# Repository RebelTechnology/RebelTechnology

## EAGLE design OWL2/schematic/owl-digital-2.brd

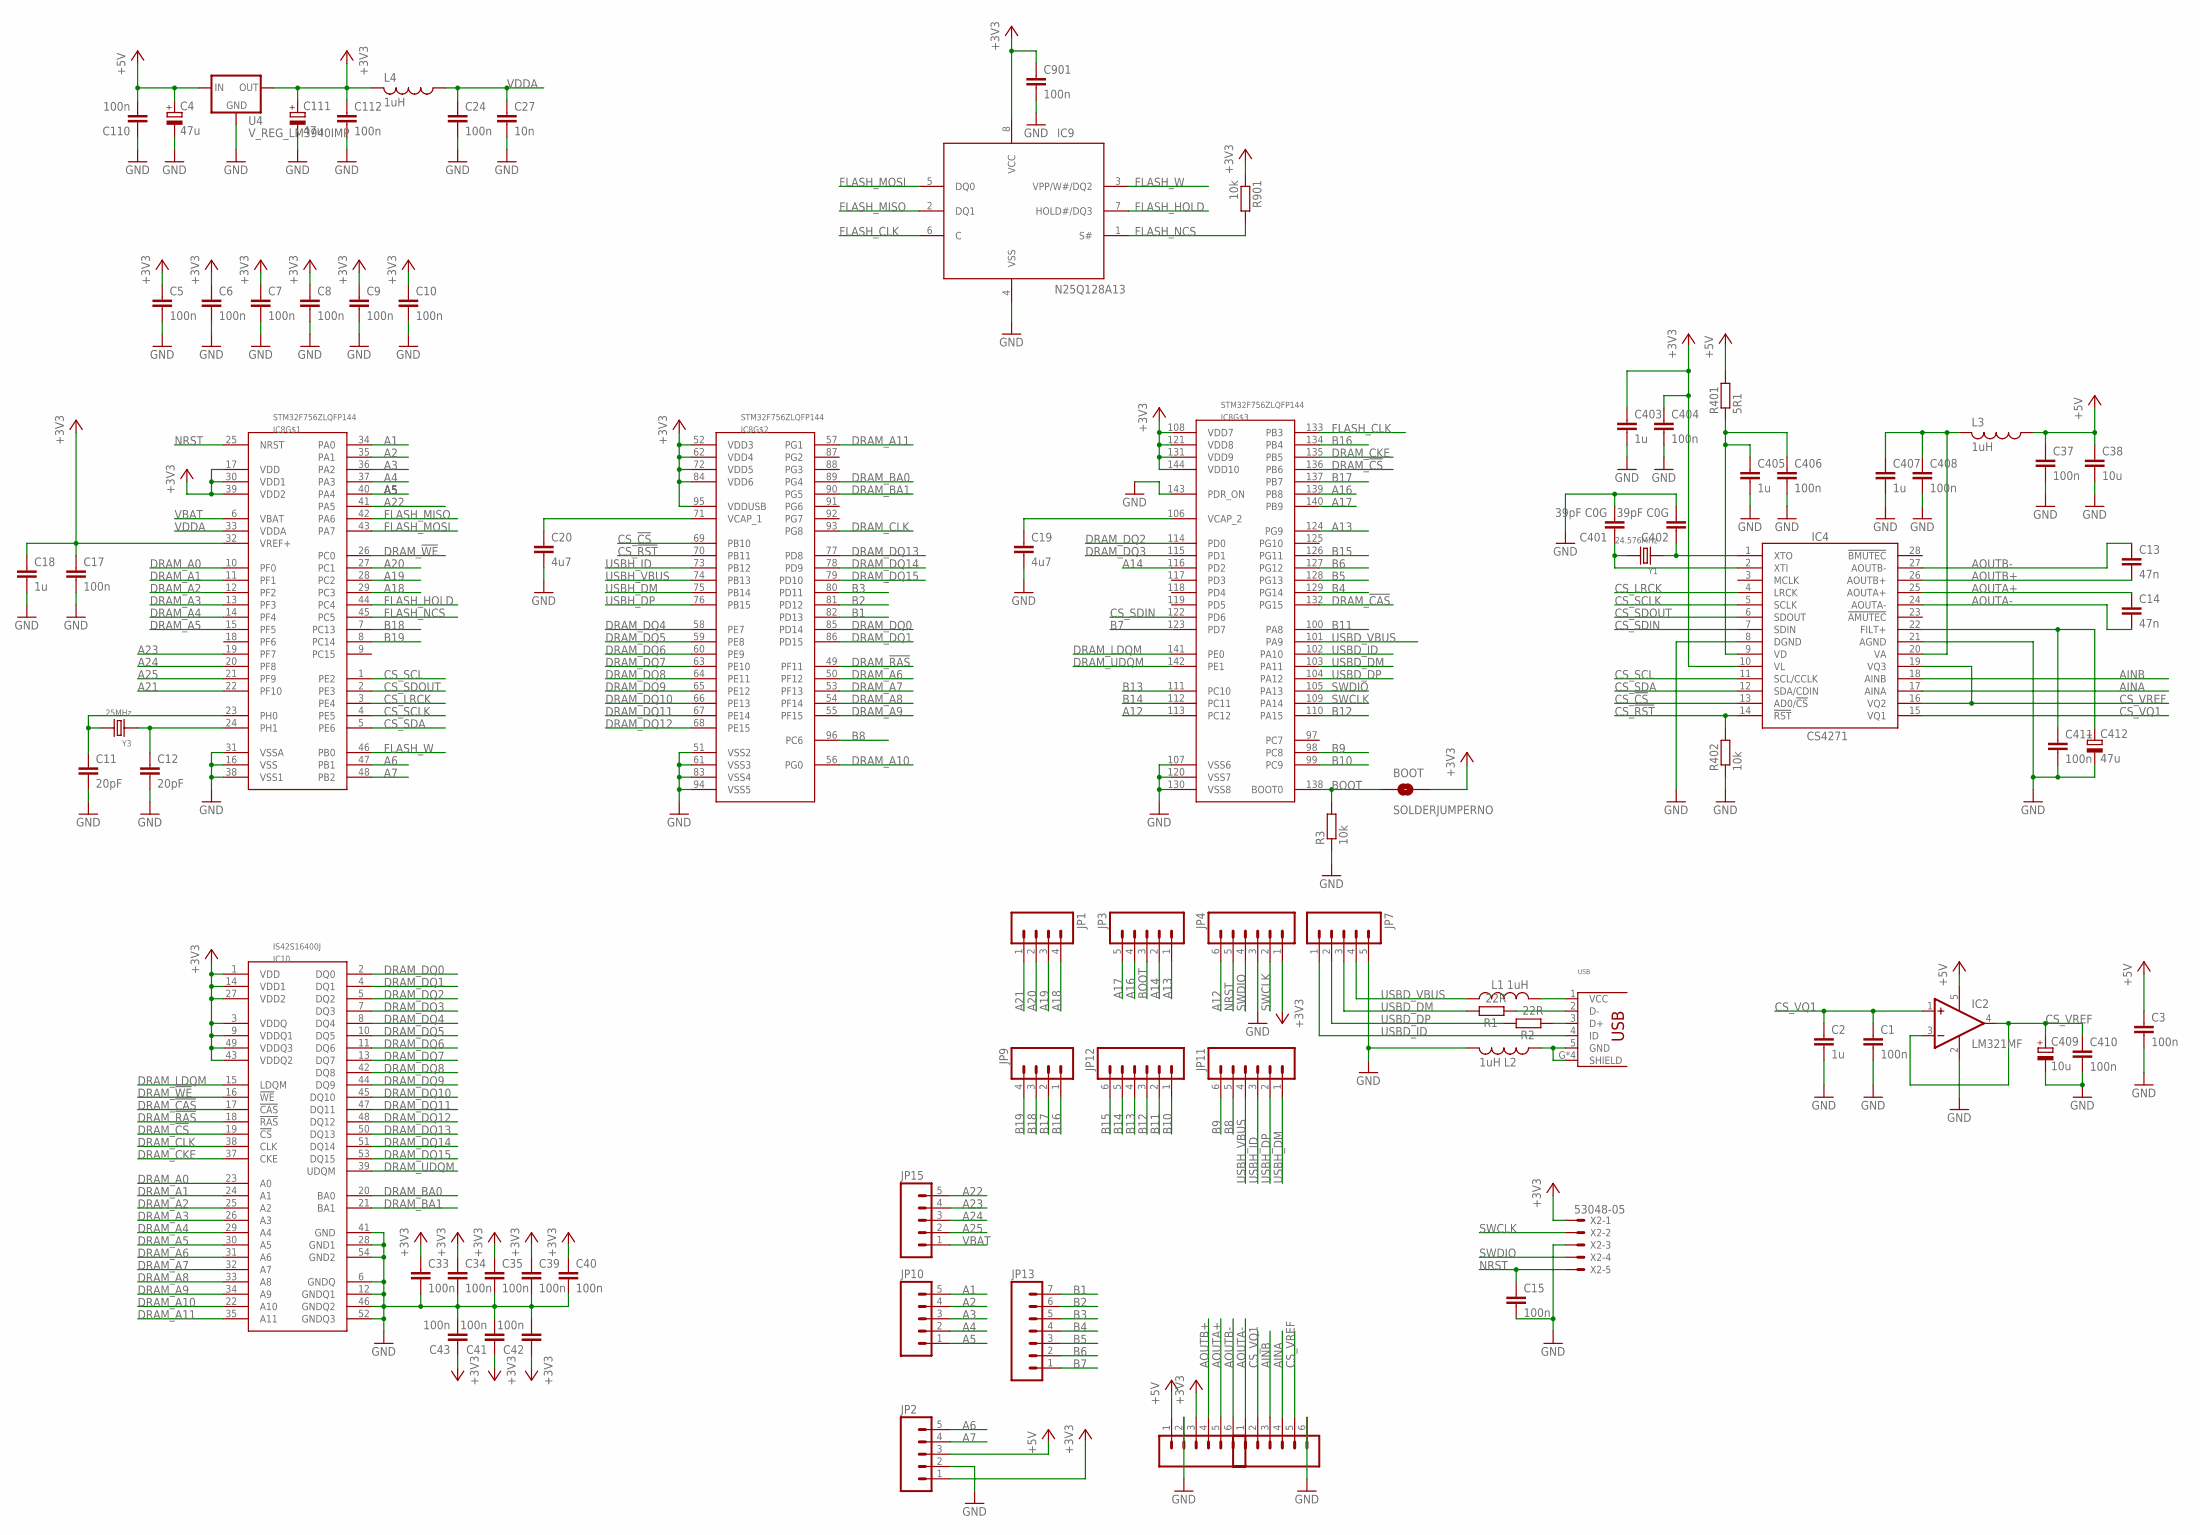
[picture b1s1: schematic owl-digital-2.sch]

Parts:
BOOT: SOLDERJUMPERNO; SJ_2S-NO
C1, C3, C5, C6, C7, C8, C9, C10, C15, C17, C24, C33, C34, C35, C37, C39, C40, C41, C42, C43, C110, C112, C404, C406, C408, C410, C411, C901: 100n; C0603
C2, C18, C403, C405, C407: 1u; C0603
C4, C111, C412: 47u; CPOL-5
C11, C12: 20pF; C0603
C13, C14: 47n; C0603
C19, C20: 4u7; C0603
C27: 10n; C0603
C38: 10u; C1206
C401, C402: 39pF C0G; C0603
C409: 10u; CPOL-5
IC2: LM321MF; SOT23-5
IC4: CS4271; TSSOP28-0.65-9.7X4.4MM
IC8: STM32F756ZLQFP144; QFP50P2200X2200X160-144N
IC9: N25Q128A13; SO8W
IC10: IS42S16400J; TSOP54-400
JP1, JP9: M04PTH; 1X04
JP2, JP3, JP7, JP10, JP15: M05PTH; 1X05
JP4, JP5, JP6, JP11, JP12: M06SIP; 1X06
JP13: M07; 1X07
L1, L2, L3, L4: 1uH; 0603
R1, R2: 22R; 0603
R3, R402, R901: 10k; 0603
R401: 5R1; 0603
U4: V_REG_LM3940IMP; SOT223
USB: USB_HRS_ZX62-B-5PA(11)MICRO.B; HRS_ZX62RD-AB-5P8
X2: 53048-05
Y1: 24.576MHz; X2-SMD-5.0X3.2X1.3MM
Y3: 25MHz; X2-SMD-5.0X3.2X1.3MM

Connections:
+3V3: BOOT.2, C5.1, C6.1, C7.1, C8.1, C9.1, C10.1, C17.1, C18.1, C33.1, C34.1, C35.1, C39.1, C40.1, C41.1, C42.1, C43.1, C111.+, C112.1, C403.1, C404.1, C901.1, IC4.10 (VL), IC8.17 (VDD), IC8.30 (VDD1), IC8.32 (VREF+), IC8.39 (VDD2), IC8.52 (VDD3), IC8.62 (VDD4), IC8.72 (VDD5), IC8.84 (VDD6), IC8.95 (VDDUSB), IC8.108 (VDD7), IC8.121 (VDD8), IC8.131 (VDD9), IC8.144 (VDD10), IC9.8 (VCC), IC10.1 (VDD), IC10.3 (VDDQ), IC10.9 (VDDQ1), IC10.14 (VDD1), IC10.27 (VDD2), IC10.43 (VDDQ2), IC10.49 (VDDQ3), JP2.1, JP4.1, JP5.3, L4.2, R901.1, U4.3 (OUT), X2.1
+5V: C3.1, C4.+, C37.1, C38.1, C110.2, IC2.5 (V+), JP2.3, JP5.1, L3.1, R401.2, U4.1 (IN)
A1: IC8.34 (PA0), JP10.5
A2: IC8.35 (PA1), JP10.4
A3: IC8.36 (PA2), JP10.3
A4: IC8.37 (PA3), JP10.2
A5: IC8.40 (PA4), JP10.1
A6: IC8.47 (PB1), JP2.5
A7: IC8.48 (PB2), JP2.4
A12: IC8.113 (PC12), JP4.6
A13: IC8.124 (PG9), JP3.1
A14: IC8.116 (PD2), JP3.2
A16: IC8.139 (PB8), JP3.4
A17: IC8.140 (PB9), JP3.5
A18: IC8.29 (PC3), JP1.4
A19: IC8.28 (PC2), JP1.3
A20: IC8.27 (PC1), JP1.2
A21: IC8.22 (PF10), JP1.1
A22: IC8.41 (PA5), JP15.5
A23: IC8.19 (PF7), JP15.4
A24: IC8.20 (PF8), JP15.3
A25: IC8.21 (PF9), JP15.2
AINA: IC4.17 (AINA), JP6.4
AINB: IC4.18 (AINB), JP6.3
AOUTA+: C14.1, IC4.25 (AOUTA+), JP5.5
AOUTA-: C14.2, IC4.24 (AOUTA-), JP6.1
AOUTB+: C13.2, IC4.26 (AOUTB+), JP5.4
AOUTB-: C13.1, IC4.27 (AOUTB-), JP5.6
B1: IC8.82 (PD13), JP13.7
B2: IC8.81 (PD12), JP13.6
B3: IC8.80 (PD11), JP13.5
B4: IC8.129 (PG14), JP13.4
B5: IC8.128 (PG13), JP13.3
B6: IC8.127 (PG12), JP13.2
B7: IC8.123 (PD7), JP13.1
B8: IC8.96 (PC6), JP11.5
B9: IC8.98 (PC8), JP11.6
B10: IC8.99 (PC9), JP12.1
B11: IC8.100 (PA8), JP12.2
B12: IC8.110 (PA15), JP12.3
B13: IC8.111 (PC10), JP12.4
B14: IC8.112 (PC11), JP12.5
B15: IC8.126 (PG11), JP12.6
B16: IC8.134 (PB4), JP9.1
B17: IC8.137 (PB7), JP9.2
B18: IC8.7 (PC13), JP9.3
B19: IC8.8 (PC14), JP9.4
BOOT: BOOT.1, IC8.138 (BOOT0), JP3.3, R3.2
CS_!CS: IC4.13 (AD0/!CS), IC8.69 (PB10)
CS_!RST: IC4.14 (!RST), IC8.70 (PB11), R402.2
CS_LRCK: IC4.4 (LRCK), IC8.3 (PE4)
CS_SCL: IC4.11 (SCL/CCLK), IC8.1 (PE2)
CS_SCLK: IC4.5 (SCLK), IC8.4 (PE5)
CS_SDA: IC4.12 (SDA/CDIN), IC8.5 (PE6)
CS_SDIN: IC4.7 (SDIN), IC8.122 (PD6)
CS_SDOUT: IC4.6 (SDOUT), IC8.2 (PE3)
CS_VQ1: C1.1, C2.1, IC2.1 (+IN), IC4.15 (VQ1), JP6.2
CS_VREF: C409.+, C410.1, IC2.3 (-IN), IC2.4 (OUT), IC4.16 (VQ2), IC4.19 (VQ3), JP6.5
DRAM_!CAS: IC8.132 (PG15), IC10.17 (!CAS)
DRAM_!CS: IC8.136 (PB6), IC10.19 (!CS)
DRAM_!RAS: IC8.49 (PF11), IC10.18 (!RAS)
DRAM_!WE: IC8.26 (PC0), IC10.16 (!WE)
DRAM_A0: IC8.10 (PF0), IC10.23 (A0)
DRAM_A1: IC8.11 (PF1), IC10.24 (A1)
DRAM_A2: IC8.12 (PF2), IC10.25 (A2)
DRAM_A3: IC8.13 (PF3), IC10.26 (A3)
DRAM_A4: IC8.14 (PF4), IC10.29 (A4)
DRAM_A5: IC8.15 (PF5), IC10.30 (A5)
DRAM_A6: IC8.50 (PF12), IC10.31 (A6)
DRAM_A7: IC8.53 (PF13), IC10.32 (A7)
DRAM_A8: IC8.54 (PF14), IC10.33 (A8)
DRAM_A9: IC8.55 (PF15), IC10.34 (A9)
DRAM_A10: IC8.56 (PG0), IC10.22 (A10)
DRAM_A11: IC8.57 (PG1), IC10.35 (A11)
DRAM_BA0: IC8.89 (PG4), IC10.20 (BA0)
DRAM_BA1: IC8.90 (PG5), IC10.21 (BA1)
DRAM_CKE: IC8.135 (PB5), IC10.37 (CKE)
DRAM_CLK: IC8.93 (PG8), IC10.38 (CLK)
DRAM_DQ0: IC8.85 (PD14), IC10.2 (DQ0)
DRAM_DQ1: IC8.86 (PD15), IC10.4 (DQ1)
DRAM_DQ2: IC8.114 (PD0), IC10.5 (DQ2)
DRAM_DQ3: IC8.115 (PD1), IC10.7 (DQ3)
DRAM_DQ4: IC8.58 (PE7), IC10.8 (DQ4)
DRAM_DQ5: IC8.59 (PE8), IC10.10 (DQ5)
DRAM_DQ6: IC8.60 (PE9), IC10.11 (DQ6)
DRAM_DQ7: IC8.63 (PE10), IC10.13 (DQ7)
DRAM_DQ8: IC8.64 (PE11), IC10.42 (DQ8)
DRAM_DQ9: IC8.65 (PE12), IC10.44 (DQ9)
DRAM_DQ10: IC8.66 (PE13), IC10.45 (DQ10)
DRAM_DQ11: IC8.67 (PE14), IC10.47 (DQ11)
DRAM_DQ12: IC8.68 (PE15), IC10.48 (DQ12)
DRAM_DQ13: IC8.77 (PD8), IC10.50 (DQ13)
DRAM_DQ14: IC8.78 (PD9), IC10.51 (DQ14)
DRAM_DQ15: IC8.79 (PD10), IC10.53 (DQ15)
DRAM_LDQM: IC8.141 (PE0), IC10.15 (LDQM)
DRAM_UDQM: IC8.142 (PE1), IC10.39 (UDQM)
FLASH_CLK: IC8.133 (PB3), IC9.6 (C)
FLASH_HOLD: IC8.44 (PC4), IC9.7 (HOLD#/DQ3)
FLASH_MISO: IC8.42 (PA6), IC9.2 (DQ1)
FLASH_MOSI: IC8.43 (PA7), IC9.5 (DQ0)
FLASH_NCS: IC8.45 (PC5), IC9.1 (S#), R901.2
FLASH_W: IC8.46 (PB0), IC9.3 (VPP/W#/DQ2)
GND: C1.2, C2.2, C3.2, C4.-, C5.2, C6.2, C7.2, C8.2, C9.2, C10.2, C11.2, C12.2, C15.2, C17.2, C18.2, C19.2, C20.2, C24.2, C27.2, C33.2, C34.2, C35.2, C37.2, C38.2, C39.2, C40.2, C41.2, C42.2, C43.2, C110.1, C111.-, C112.2, C401.2, C402.2, C403.2, C404.2, C405.2, C406.2, C407.2, C408.2, C409.-, C410.2, C411.2, C412.-, C901.2, IC2.2 (V-), IC4.8 (DGND), IC4.21 (AGND), IC8.16 (VSS), IC8.31 (VSSA), IC8.38 (VSS1), IC8.51 (VSS2), IC8.61 (VSS3), IC8.83 (VSS4), IC8.94 (VSS5), IC8.107 (VSS6), IC8.120 (VSS7), IC8.130 (VSS8), IC8.143 (PDR_ON), IC9.4 (VSS), IC10.6 (GNDQ), IC10.12 (GNDQ1), IC10.28 (GND1), IC10.41 (GND), IC10.46 (GNDQ2), IC10.52 (GNDQ3), IC10.54 (GND2), JP2.2, JP4.3, JP5.2, JP6.6, JP7.5, L2.2, R3.1, R402.1, U4.2 (GND), X2.3
unnamed: L2.1, USB.5 (GND), USB.G (SHIELD), USB.G2 (SHIELD), USB.G3 (SHIELD), USB.G4 (SHIELD)
unnamed: L1.2, USB.1 (VCC)
unnamed: R2.1, USB.3 (D+)
unnamed: R1.1, USB.2 (D-)
unnamed: C12.1, IC8.24 (PH1), Y3.1
unnamed: C11.1, IC8.23 (PH0), Y3.2
unnamed: C402.1, IC4.1 (XTO), Y1.1
unnamed: C411.1, C412.+, IC4.22 (FILT+)
unnamed: C401.1, IC4.2 (XTI), Y1.2
unnamed: C19.1, IC8.106 (VCAP_2)
unnamed: C20.1, IC8.71 (VCAP_1)
NRST: C15.1, IC8.25 (NRST), JP4.5, X2.5
SWCLK: IC8.109 (PA14), JP4.2, X2.2
SWDIO: IC8.105 (PA13), JP4.4, X2.4
USBD_DM: IC8.103 (PA11), JP7.3, R1.2
USBD_DP: IC8.104 (PA12), JP7.2, R2.2
USBD_ID: IC8.102 (PA10), JP7.1, USB.4 (ID)
USBD_VBUS: IC8.101 (PA9), JP7.4, L1.1
USBH_DM: IC8.75 (PB14), JP11.1
USBH_DP: IC8.76 (PB15), JP11.2
USBH_ID: IC8.73 (PB12), JP11.3
USBH_VBUS: IC8.74 (PB13), JP11.4
VA: C407.1, C408.1, IC4.20 (VA), L3.2
VBAT: IC8.6 (VBAT), JP15.1
VD: C405.1, C406.1, IC4.9 (VD), R401.1
VDDA: C24.1, C27.1, IC8.33 (VDDA), L4.1

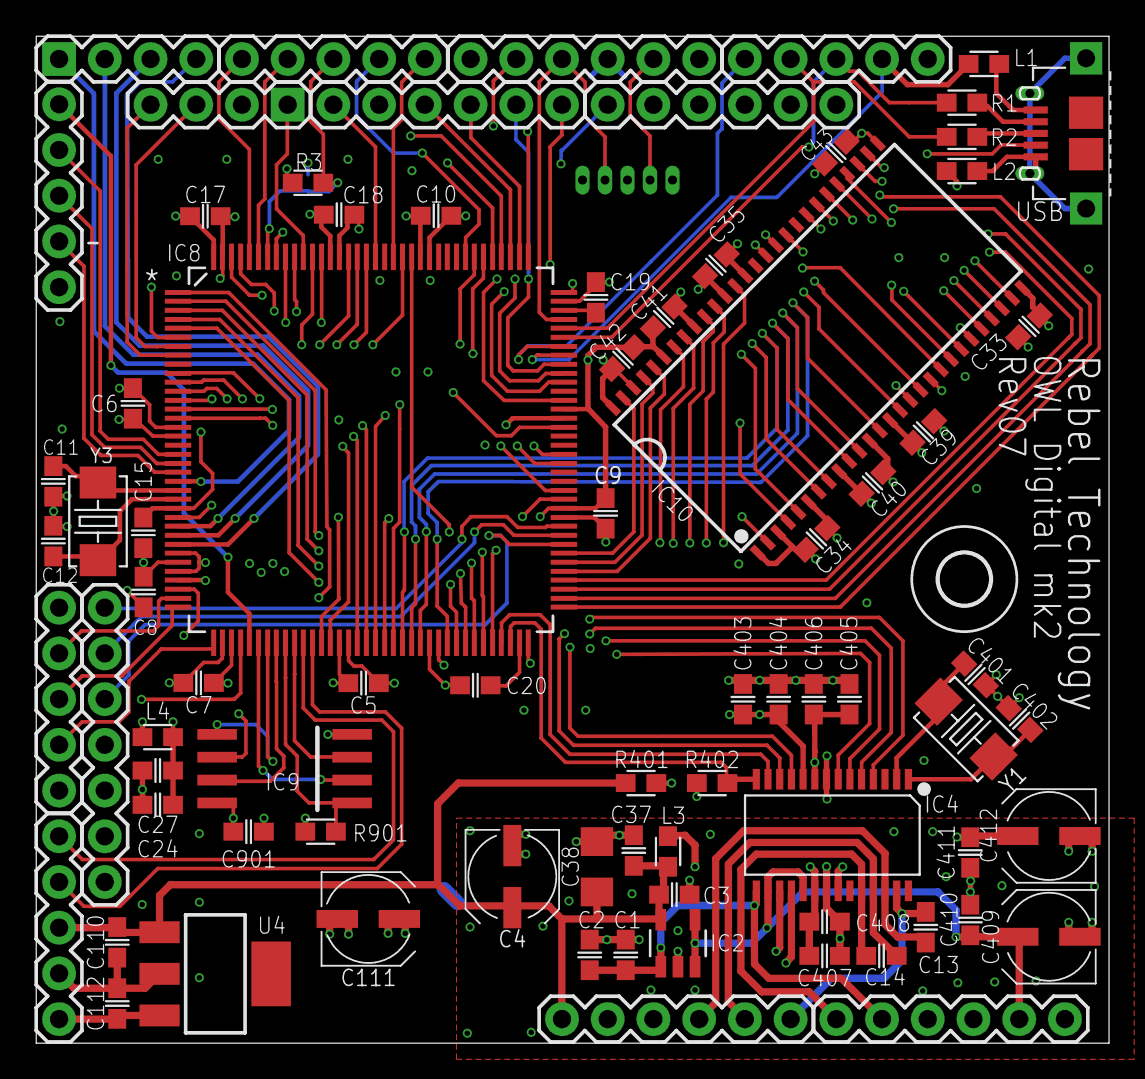
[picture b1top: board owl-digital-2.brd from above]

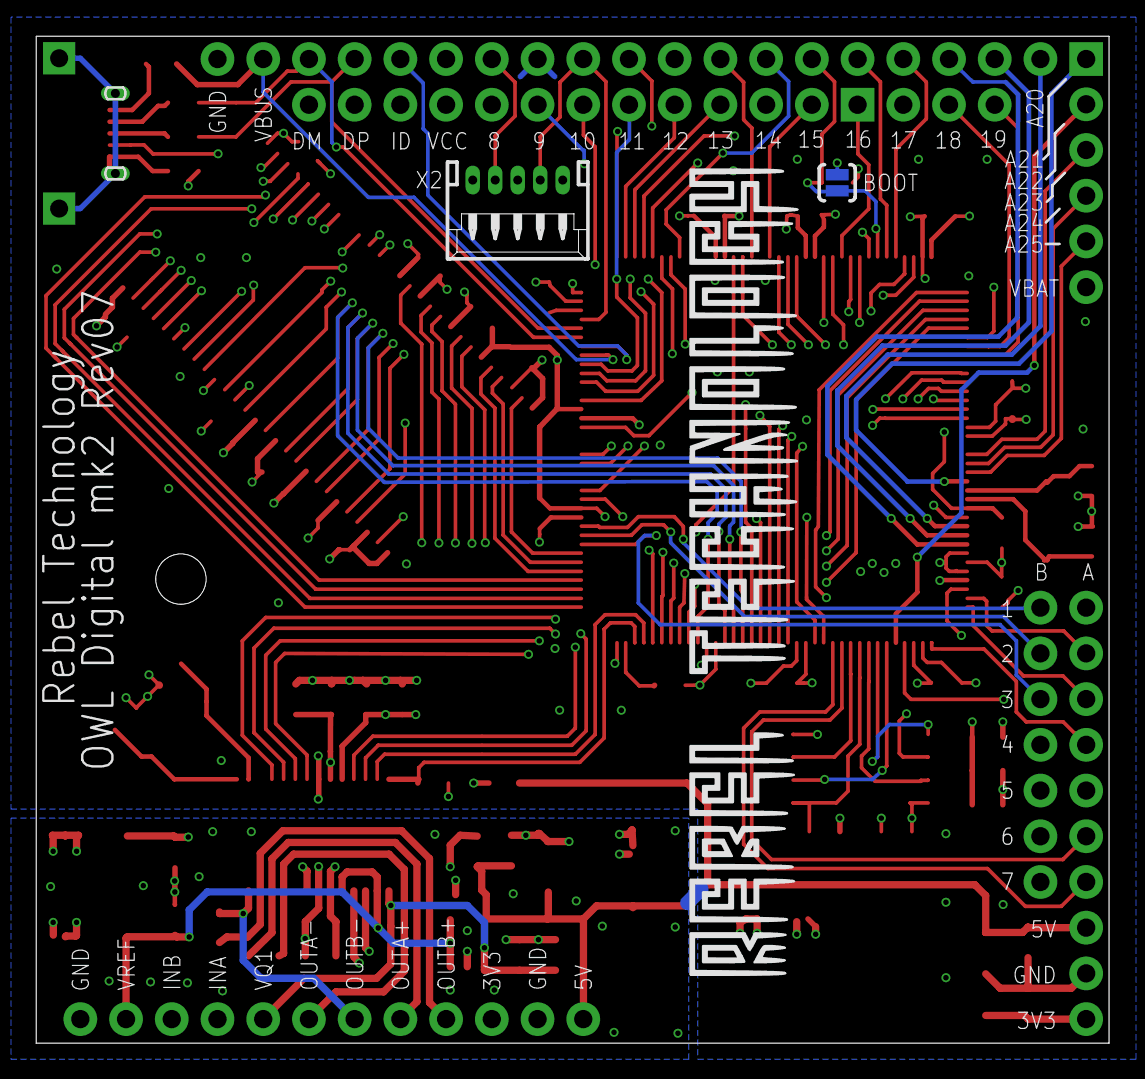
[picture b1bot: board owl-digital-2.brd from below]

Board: 4 copper layers, 59.6 x 55.9 mm, 82 parts (2 on the bottom side), 129 nets.

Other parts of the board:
U$1: 2,8

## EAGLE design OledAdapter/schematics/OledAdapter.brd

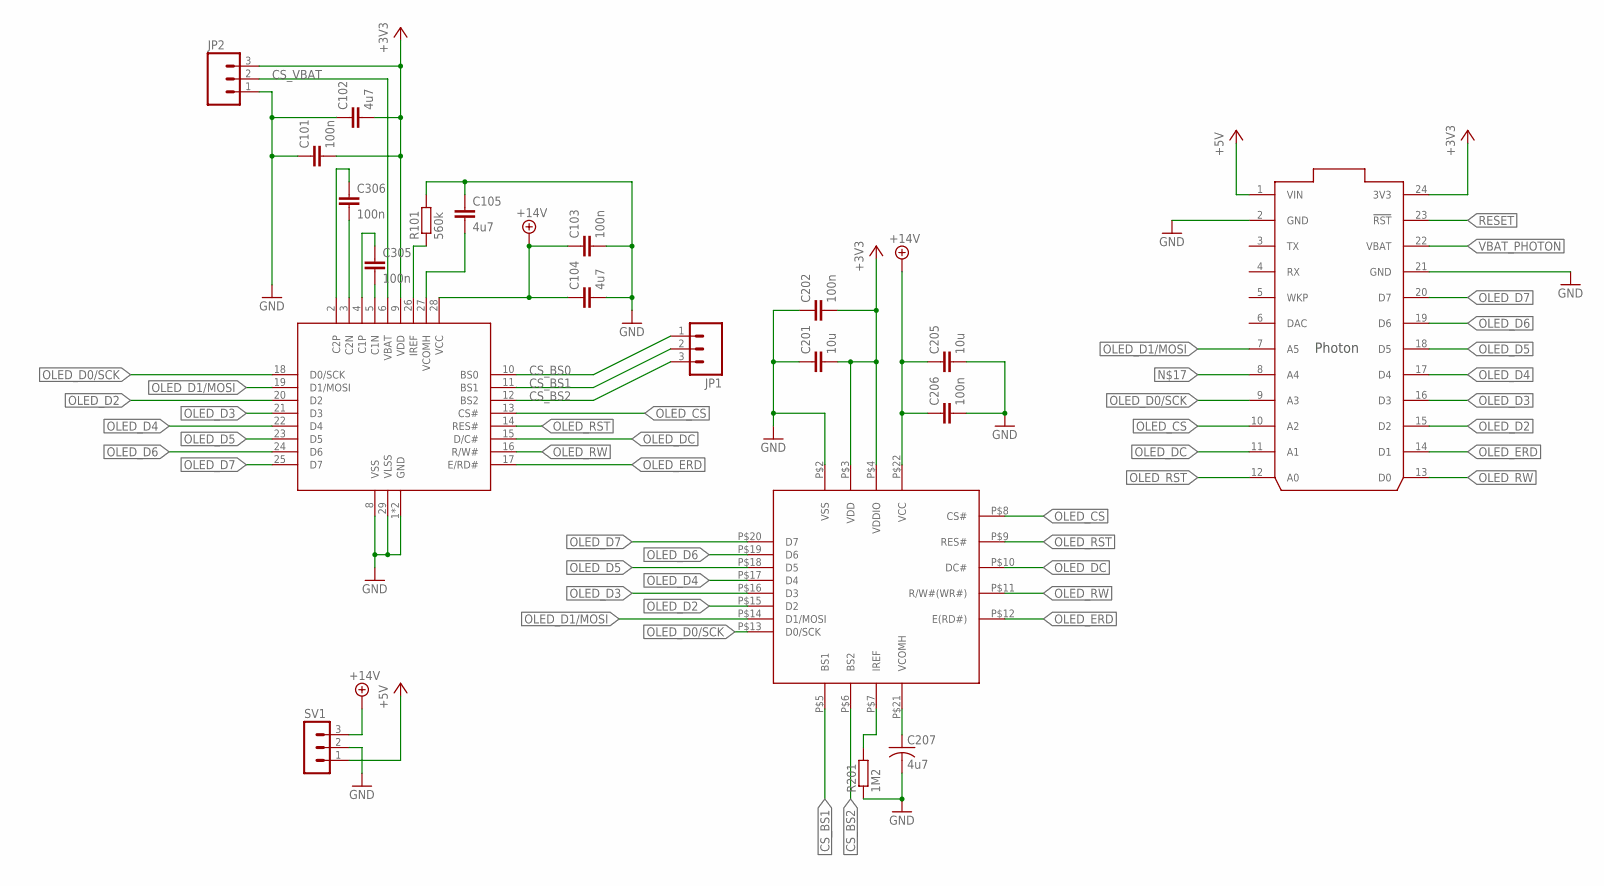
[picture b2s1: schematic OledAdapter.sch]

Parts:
C101, C103, C202, C206, C305, C306: 100n; C0603
C102, C104, C105, C207: 4u7; C0603
C201, C205: 10u; C0603
JP1, JP2: M03PTH; 1X03
R101: 560k; R0603
R201: 1M2; R0603
SV1: MA03-1
U$1: MCOT128064NZ-YM
U$2: PHOTON_WITH_HEADERS; PHOTON
U$3: MCOT096064AZ-RGBM

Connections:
+3V3: C101.2, C102.2, C201.2, C202.2, JP2.3, U$1.9 (VDD), U$2.24 (3V3), U$3.P$3 (VDD), U$3.P$4 (VDDIO)
+5V: SV1.1, U$2.1 (VIN)
+14V: C103.1, C104.1, C205.1, C206.1, SV1.3, U$1.28 (VCC), U$3.P$22 (VCC)
CS_BS0: JP1.1, U$1.10 (BS0)
CS_BS1: JP1.2, U$1.11 (BS1), U$3.P$5 (BS1)
CS_BS2: JP1.3, U$1.12 (BS2), U$3.P$6 (BS2)
CS_VBAT: JP2.2, U$1.6 (VBAT)
GND: C101.1, C102.1, C103.2, C104.2, C105.1, C201.1, C202.1, C205.2, C206.2, C207.2, JP2.1, R101.2, R201.1, SV1.2, U$1.1 (GND), U$1.8 (VSS), U$1.29 (VLSS), U$1.30 (GND), U$2.2 (GND), U$2.21 (GND), U$3.P$2 (VSS)
unnamed: C305.2, U$1.5 (C1N)
unnamed: C305.1, U$1.4 (C1P)
unnamed: C306.2, U$1.3 (C2N)
unnamed: R101.1, U$1.26 (IREF)
unnamed: C207.1, U$3.P$21 (VCOMH)
unnamed: C105.2, U$1.27 (VCOMH)
unnamed: R201.2, U$3.P$7 (IREF)
unnamed: C306.1, U$1.2 (C2P)
OLED_CS: U$1.13 (CS#), U$2.10 (A2), U$3.P$8 (CS#)
OLED_D0/SCK: U$1.18 (D0/SCK), U$2.9 (A3), U$3.P$13 (D0/SCK)
OLED_D1/MOSI: U$1.19 (D1/MOSI), U$2.7 (A5), U$3.P$14 (D1/MOSI)
OLED_D2: U$1.20 (D2), U$2.15 (D2), U$3.P$15 (D2)
OLED_D3: U$1.21 (D3), U$2.16 (D3), U$3.P$16 (D3)
OLED_D4: U$1.22 (D4), U$2.17 (D4), U$3.P$17 (D4)
OLED_D5: U$1.23 (D5), U$2.18 (D5), U$3.P$18 (D5)
OLED_D6: U$1.24 (D6), U$2.19 (D6), U$3.P$19 (D6)
OLED_D7: U$1.25 (D7), U$2.20 (D7), U$3.P$20 (D7)
OLED_DC: U$1.15 (D/C#), U$2.11 (A1), U$3.P$10 (DC#)
OLED_ERD: U$1.17 (E/RD#), U$2.14 (D1), U$3.P$12 (E(RD#))
OLED_RST: U$1.14 (RES#), U$2.12 (A0), U$3.P$9 (RES#)
OLED_RW: U$1.16 (R/W#), U$2.13 (D0), U$3.P$11 (R/W#(WR#))
RESET: U$2.23 (!RST)
VBAT_PHOTON: U$2.22 (VBAT)

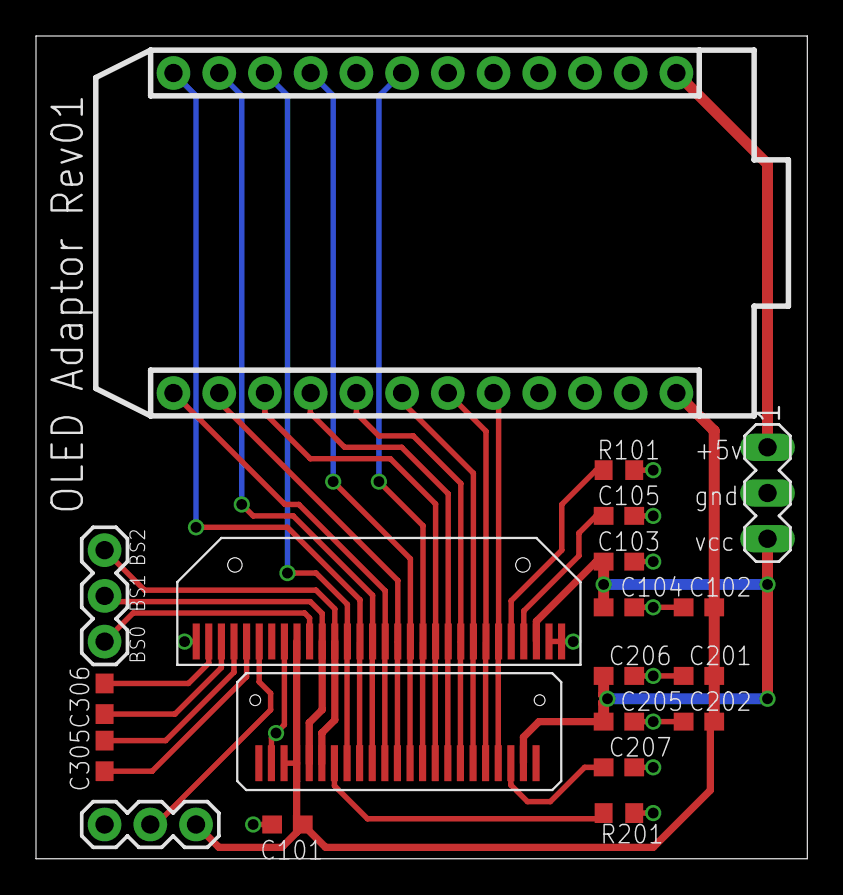
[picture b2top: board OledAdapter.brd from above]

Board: 2 copper layers, 42.9 x 45.7 mm, 20 parts (0 on the bottom side), 29 nets.

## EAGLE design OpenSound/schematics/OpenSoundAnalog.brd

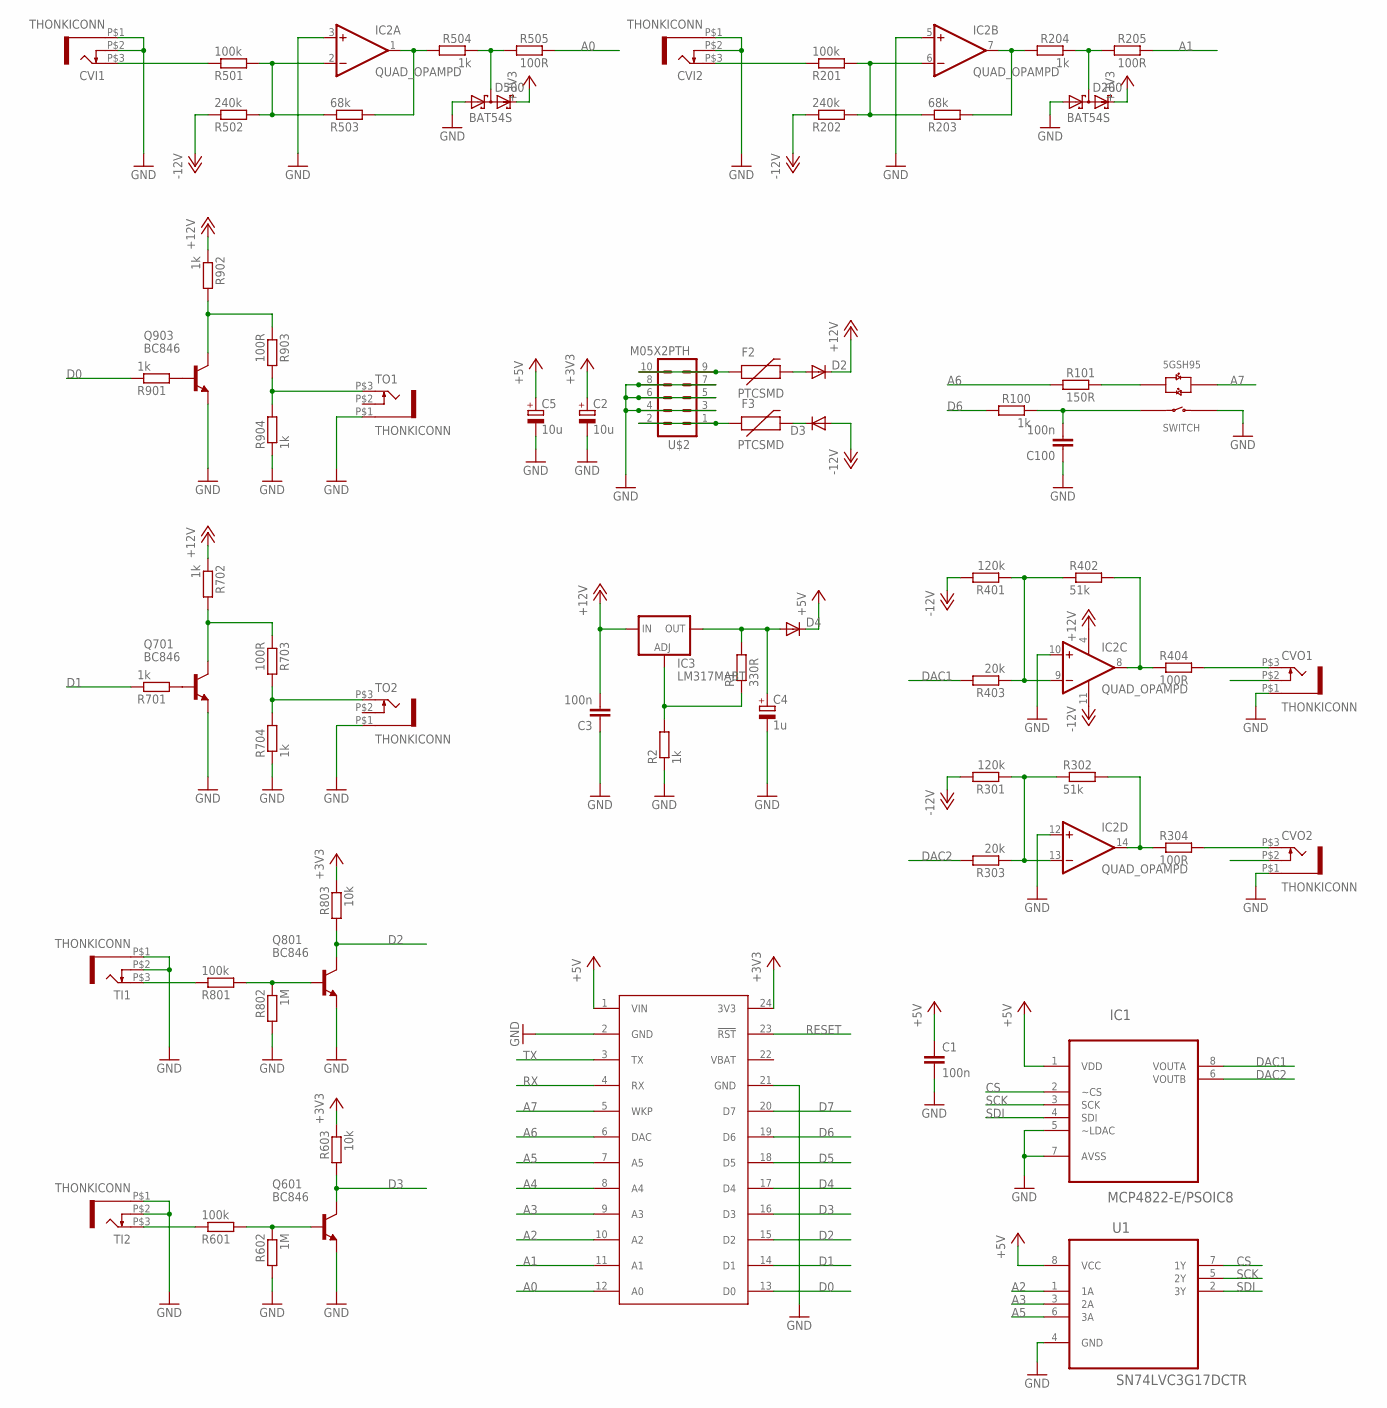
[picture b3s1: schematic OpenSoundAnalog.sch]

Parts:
C1, C3, C100: 100n; C0603
C2, C5: 10u; SANYO-OSCON_SMD_A5
C4: 1u; SANYO-OSCON_SMD_A5
CVI1, CVI2: THONKICONN
CVO1, CVO2: THONKICONN
D2, D3, D4: DIODESMA; SMA-DIODE
D200, D500: BAT54S; SOT23
F2, F3: PTCSMD; PTC-1206
IC1: MCP4822-E/PSOIC8; SOIC8
IC2: QUAD_OPAMPD; SO14
IC3: LM317MABT; TO220L1
Q601, Q701, Q801, Q903: BC846; SOT23
R1: 330R; 0603
R2, R100, R204, R504, R701, R702, R704, R901, R902, R904: 1k; 0603
R101: 150R; 0603
R201, R501, R601, R801: 100k; 0603
R202, R502: 240k; 0603
R203, R503: 68k; 0603
R205, R304, R404, R505, R703, R903: 100R; 0603
R301, R401: 120k; 0603
R302, R402: 51k; 0603
R303, R403: 20k; 0603
R602, R802: 1M; 0603
R603, R803: 10k; 0603
SPARK: SPARK_CORE
TI1, TI2: THONKICONN
TO1, TO2: THONKICONN
U1: SN74LVC3G17DCTR; SOP65P400X130-8N
U$1: 5GTH9
U$2: M05X2PTH; AVR_ICSP

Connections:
+3V3: C2.+, D200.2 (C2), D500.2 (C2), R603.1, R803.1, SPARK.24 (3V3)
+5V: C1.1, C5.+, D4.C, IC1.1 (VDD), SPARK.1 (VIN), U1.8 (VCC)
+12V: C3.2, D2.C, IC2.4 (V+), IC3.3 (IN), R702.1, R902.1
-12V: D3.A, IC2.11 (V-), R202.1, R301.2, R401.2, R502.1
A0: R505.1, SPARK.12 (A0)
A1: R205.1, SPARK.11 (A1)
A2: SPARK.10 (A2), U1.1 (1A)
A3: SPARK.9 (A3), U1.3 (2A)
A4: SPARK.8 (A4)
A5: SPARK.7 (A5), U1.6 (3A)
A6: R101.2, SPARK.6 (DAC)
A7: SPARK.5 (WKP), U$1.+3 (LED_R+)
CS: IC1.2 (~CS), U1.7 (1Y)
D0: R901.1, SPARK.13 (D0)
D1: R701.1, SPARK.14 (D1)
D2: Q801.3 (C), R803.2, SPARK.15 (D2)
D3: Q601.3 (C), R603.2, SPARK.16 (D3)
D4: SPARK.17 (D4)
D5: SPARK.18 (D5)
D6: R100.2, SPARK.19 (D6)
D7: SPARK.20 (D7)
DAC1: IC1.8 (VOUTA), R403.2
DAC2: IC1.6 (VOUTB), R303.2
GND: C1.2, C2.-, C3.1, C4.-, C5.-, C100.1, CVI1.P$1 (5), CVI1.P$2 (4), CVI2.P$1 (5), CVI2.P$2 (4), CVO1.P$1 (5), CVO2.P$1 (5), D200.1 (A1), D500.1 (A1), IC1.5 (~LDAC), IC1.7 (AVSS), IC2.3 (+IN), IC2.5 (+IN), IC2.10 (+IN), IC2.12 (+IN), Q601.2 (E), Q701.2 (E), Q801.2 (E), Q903.2 (E), R2.1, R602.2, R704.1, R802.2, R904.1, SPARK.2 (GND), SPARK.21 (GND), TI1.P$1 (5), TI1.P$2 (4), TI2.P$1 (5), TI2.P$2 (4), TO1.P$1 (5), TO2.P$1 (5), U1.4 (GND), U$1.1 (SWITCH_B), U$2.3, U$2.4, U$2.5, U$2.6, U$2.7, U$2.8
unnamed: R703.2, R704.2, TO2.P$3 (3)
unnamed: Q903.1 (B), R901.2
unnamed: IC2.14 (OUT), R302.2, R304.1
unnamed: Q903.3 (C), R902.2, R903.1
unnamed: R903.2, R904.2, TO1.P$3 (3)
unnamed: F3.1, U$2.1, U$2.2
unnamed: IC2.8 (OUT), R402.2, R404.1
unnamed: Q801.1 (B), R801.2, R802.1
unnamed: R801.1, TI1.P$3 (3)
unnamed: CVI1.P$3 (3), R501.1
unnamed: IC2.9 (-IN), R401.1, R402.1, R403.1
unnamed: IC2.2 (-IN), R501.2, R502.2, R503.1
unnamed: IC2.13 (-IN), R301.1, R302.1, R303.1
unnamed: D500.3 (C1A2), R504.1, R505.2
unnamed: IC2.1 (OUT), R503.2, R504.2
unnamed: CVI2.P$3 (3), R201.1
unnamed: IC3.1 (ADJ), R1.1, R2.2
unnamed: IC2.6 (-IN), R201.2, R202.2, R203.1
unnamed: C4.+, D4.A, IC3.2 (OUT), R1.2
unnamed: IC2.7 (OUT), R203.2, R204.2
unnamed: R601.1, TI2.P$3 (3)
unnamed: D200.3 (C1A2), R204.1, R205.2
unnamed: D3.C, F3.2
unnamed: D2.A, F2.2
unnamed: Q601.1 (B), R601.2, R602.1
unnamed: R101.1, U$1.-2 (LED_G+)
unnamed: CVO1.P$3 (3), R404.2
unnamed: CVO2.P$3 (3), R304.2
unnamed: Q701.1 (B), R701.2
unnamed: Q701.3 (C), R702.2, R703.1
unnamed: F2.1, U$2.9, U$2.10
RESET: SPARK.23 (!RST)
RX: SPARK.4 (RX)
SCK: IC1.3 (SCK), U1.5 (2Y)
SDI: IC1.4 (SDI), U1.2 (3Y)
SWITCH_A: C100.2, R100.1, U$1.4 (SWITCH_A)
TX: SPARK.3 (TX)
VBAT: SPARK.22 (VBAT)

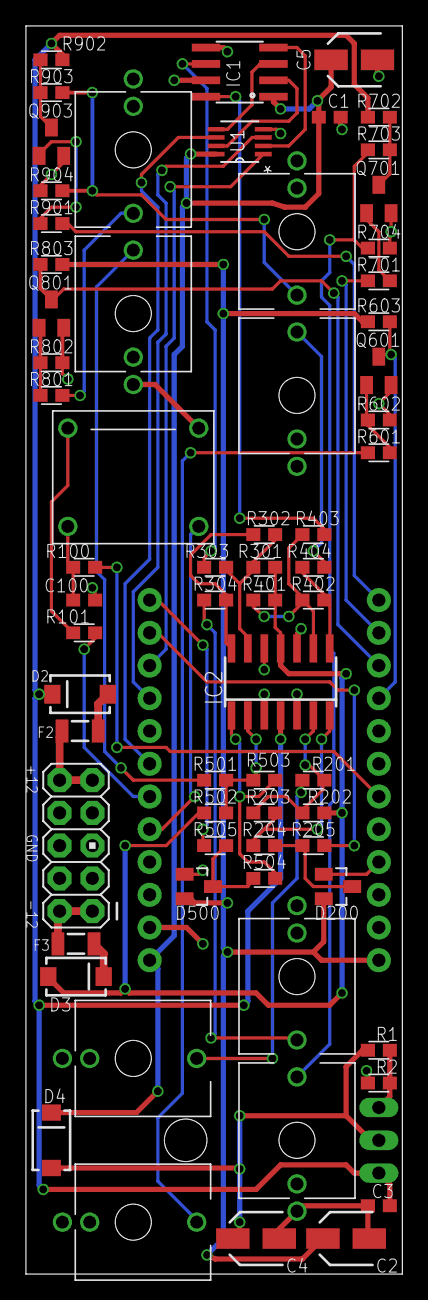
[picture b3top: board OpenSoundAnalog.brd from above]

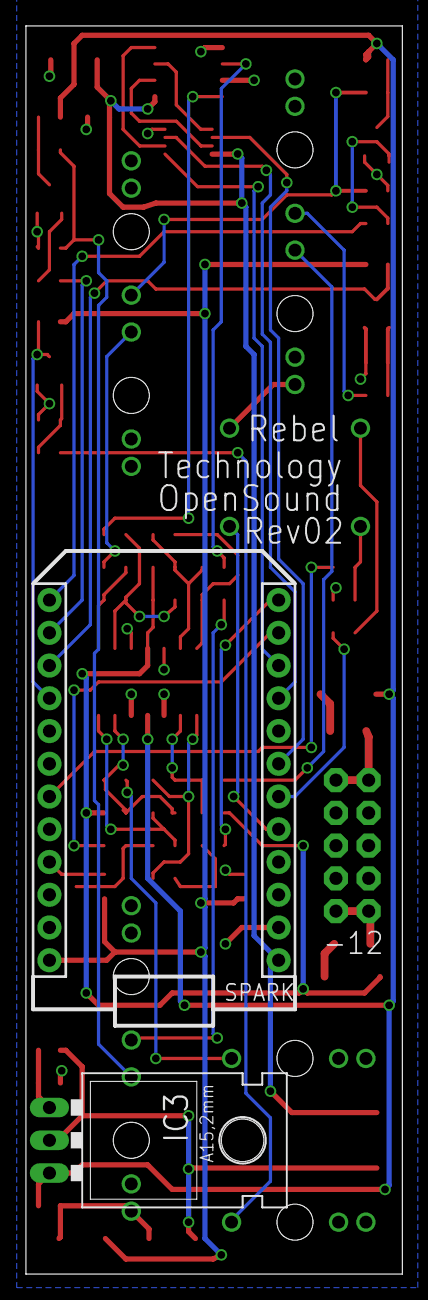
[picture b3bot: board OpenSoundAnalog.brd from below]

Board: 2 copper layers, 29.2 x 96.8 mm, 68 parts (2 on the bottom side), 54 nets.

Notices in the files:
parts and their libraries:
SparkFun: Licensing: CC v3.0 Share-Alike You are welcome to use this library for commercial purposes.
SparkFun-Connectors: Licensing: Creative Commons ShareAlike 4.0 International - https://creativecommons.org/licenses/by-sa/4.0
